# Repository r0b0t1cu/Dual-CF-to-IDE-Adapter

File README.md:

# Dual CF-to-IDE Adapter

A dual CompactFlash-to-IDE adapter designed to connect two CF cards to a standard 40-pin IDE interface. Each CF slot can be configured independently as **Master**, **Slave**, or **Cable Select**. The board also provides selectable CF supply voltage and selectable power input.

The project is intended for vintage-computing and other systems that use an IDE interface.

## Features

- Two CompactFlash card slots (Slot A and Slot B).
- Independent Master / Slave / Cable Select configuration for each slot.
- Selectable CF supply voltage: **5 V or 3.3 V**.
- Selectable power source: external +5 V input or power from IDE pin 20.
- Four status LEDs:
  - **POWER** – board power indication.
  - **MASTER** – lit when a card is present in slot A.
  - **SLAVE** – lit when a card is present in slot B.
  - **ACTIVITY** – drive activity indication (shared DASP# line; lit during access by either card, if the card drives DASP#).
- Polyfuse protection on the power input.
- KiCad design files, schematic, BOM, assembly documentation and PCB manufacturing files included.

## Configuration

**Set the jumpers before powering the adapter.**

### JP1 – Power Select

Selects the source for the board's +5 V supply:

| JP1 position | Power source |
|---|---|
| Pins 1–2 | External +5 V input via J5 |
| Pins 2–3 | IDE connector pin 20 |

J5 is the two-pin external power connector and is marked `+5V` on the PCB. Use only the selected power source; do not connect external power and IDE pin-20 power at the same time.

### JP2 – CF supply voltage

Selects the supply voltage provided to the CF interface:

| JP2 position | CF supply |
|---|---|
| Pins 1–2 | 5 V |
| Pins 2–3 | 3.3 V |

**Check the voltage requirement of your CF card before setting JP2.** Do not assume that every CompactFlash card accepts both supply voltages.

### JP3 – Slot A (Master/Slave)

| JP3 position | Slot A configuration |
|---|---|
| Pins 1–2 | Master |
| Pins 2–3 | Cable Select |
| Open (no jumper) | Slave |

### JP4 – Slot B (Master/Slave)

| JP4 position | Slot B configuration |
|---|---|
| Pins 1–2 | Master |
| Pins 2–3 | Cable Select |
| Open (no jumper) | Slave |

The two slots have independent device-select jumpers. When using both cards on the same IDE channel, configure them so that they do not both claim the same device role (for example, one Master and the other Slave), subject to the host system's IDE support.
The CF A / CF B LEDs follow the physical slot, not the Master/Slave role set by JP3/JP4.

## Connectors and indicators

| Reference | Description |
|---|---|
| J2 | 40-pin IDE interface |
| J3 | CompactFlash Slot A |
| J4 | CompactFlash Slot B |
| J5 | External +5 V power input |
| JP1 | Power-source selection |
| JP2 | CF supply-voltage selection |
| JP3 | Slot A device selection |
| JP4 | Slot B device selection |
| D2 | POWER LED |
| D3 | CF A card-present LED |
| D4 | CF B card-present LED |
| D5 | ACTIVITY LED |

---

If you enjoy my projects and would like to support my work, you can do so through PCBWay. You can also order the PCBs for this project directly from the link below. Every bit of support is appreciated!

<p>
  
</p>

---

## Bill of Materials

The component list is available in two formats:

- [`bom/ibom.html`](bom/ibom.html) – interactive Bill of Materials.
- [`production/bom.csv`](production/bom.csv) – CSV component list.

The BOM includes the two CF connectors, IDE socket, power and configuration headers, AMS1117-3.3 regulator, capacitors, resistors, LEDs and a polyfuse. Check the BOM and the PCB silkscreen when sourcing and assembling components.

## PCB fabrication

The `production/` directory contains the fabrication archive and supporting production data:

- `Dual-CF-to-IDE_Adapter_v1.zip` – PCB manufacturing files.
- `bom.csv` – component list.
- `designators.csv` – component designators.
- `netlist.ipc` – IPC netlist.
- `positions.csv` – component placement data.

Confirm the fabrication archive and the requirements of your PCB manufacturer before placing an order.

## Assembly and first power-up

1. Assemble the PCB using the schematic and BOM.
2. Check the orientation of the CF connectors, LEDs, electrolytic capacitors and voltage regulator.
3. Inspect the board for solder bridges, shorts and incorrect component placement.
4. Set JP1 to the intended power source.
5. Set JP2 to the voltage required by the CF card(s).
6. Set JP3 and JP4 for the intended Master/Slave/Cable Select arrangement.
7. Verify the selected supply voltage and polarity before inserting cards and connecting the adapter to the host.

If you are unsure about the host's IDE pin-20 wiring or the CF card's voltage requirements, verify these details before applying power.

## Documentation and photos

- [Schematic PDF](doc/Dual-CF-to-IDE_Adapter_v1.pdf)
- [Interactive BOM](bom/ibom.html)

Board photographs:

## Design files

The hardware design is provided as KiCad project, schematic and PCB files in `Dual-CF-to-IDE_Adapter_v1/`. (needs KiCad 10)

## License

The hardware design files in this project are released under the **CERN Open Hardware Licence Version 2 – Strongly Reciprocal (CERN-OHL-S-2.0)**. See the [`LICENSE`](LICENSE) file for the complete licence text.

This licence allows the design to be used, studied, modified, manufactured and redistributed, including commercially. If you distribute modified design files or products based on this design, the licence requires you to make the corresponding complete source available under the same licence and preserve the applicable notices.

Third-party components, libraries and other materials included in the repository may be subject to their own licences; those remain applicable to their respective materials.

Copyright (C) 2026 r0b0t1cu

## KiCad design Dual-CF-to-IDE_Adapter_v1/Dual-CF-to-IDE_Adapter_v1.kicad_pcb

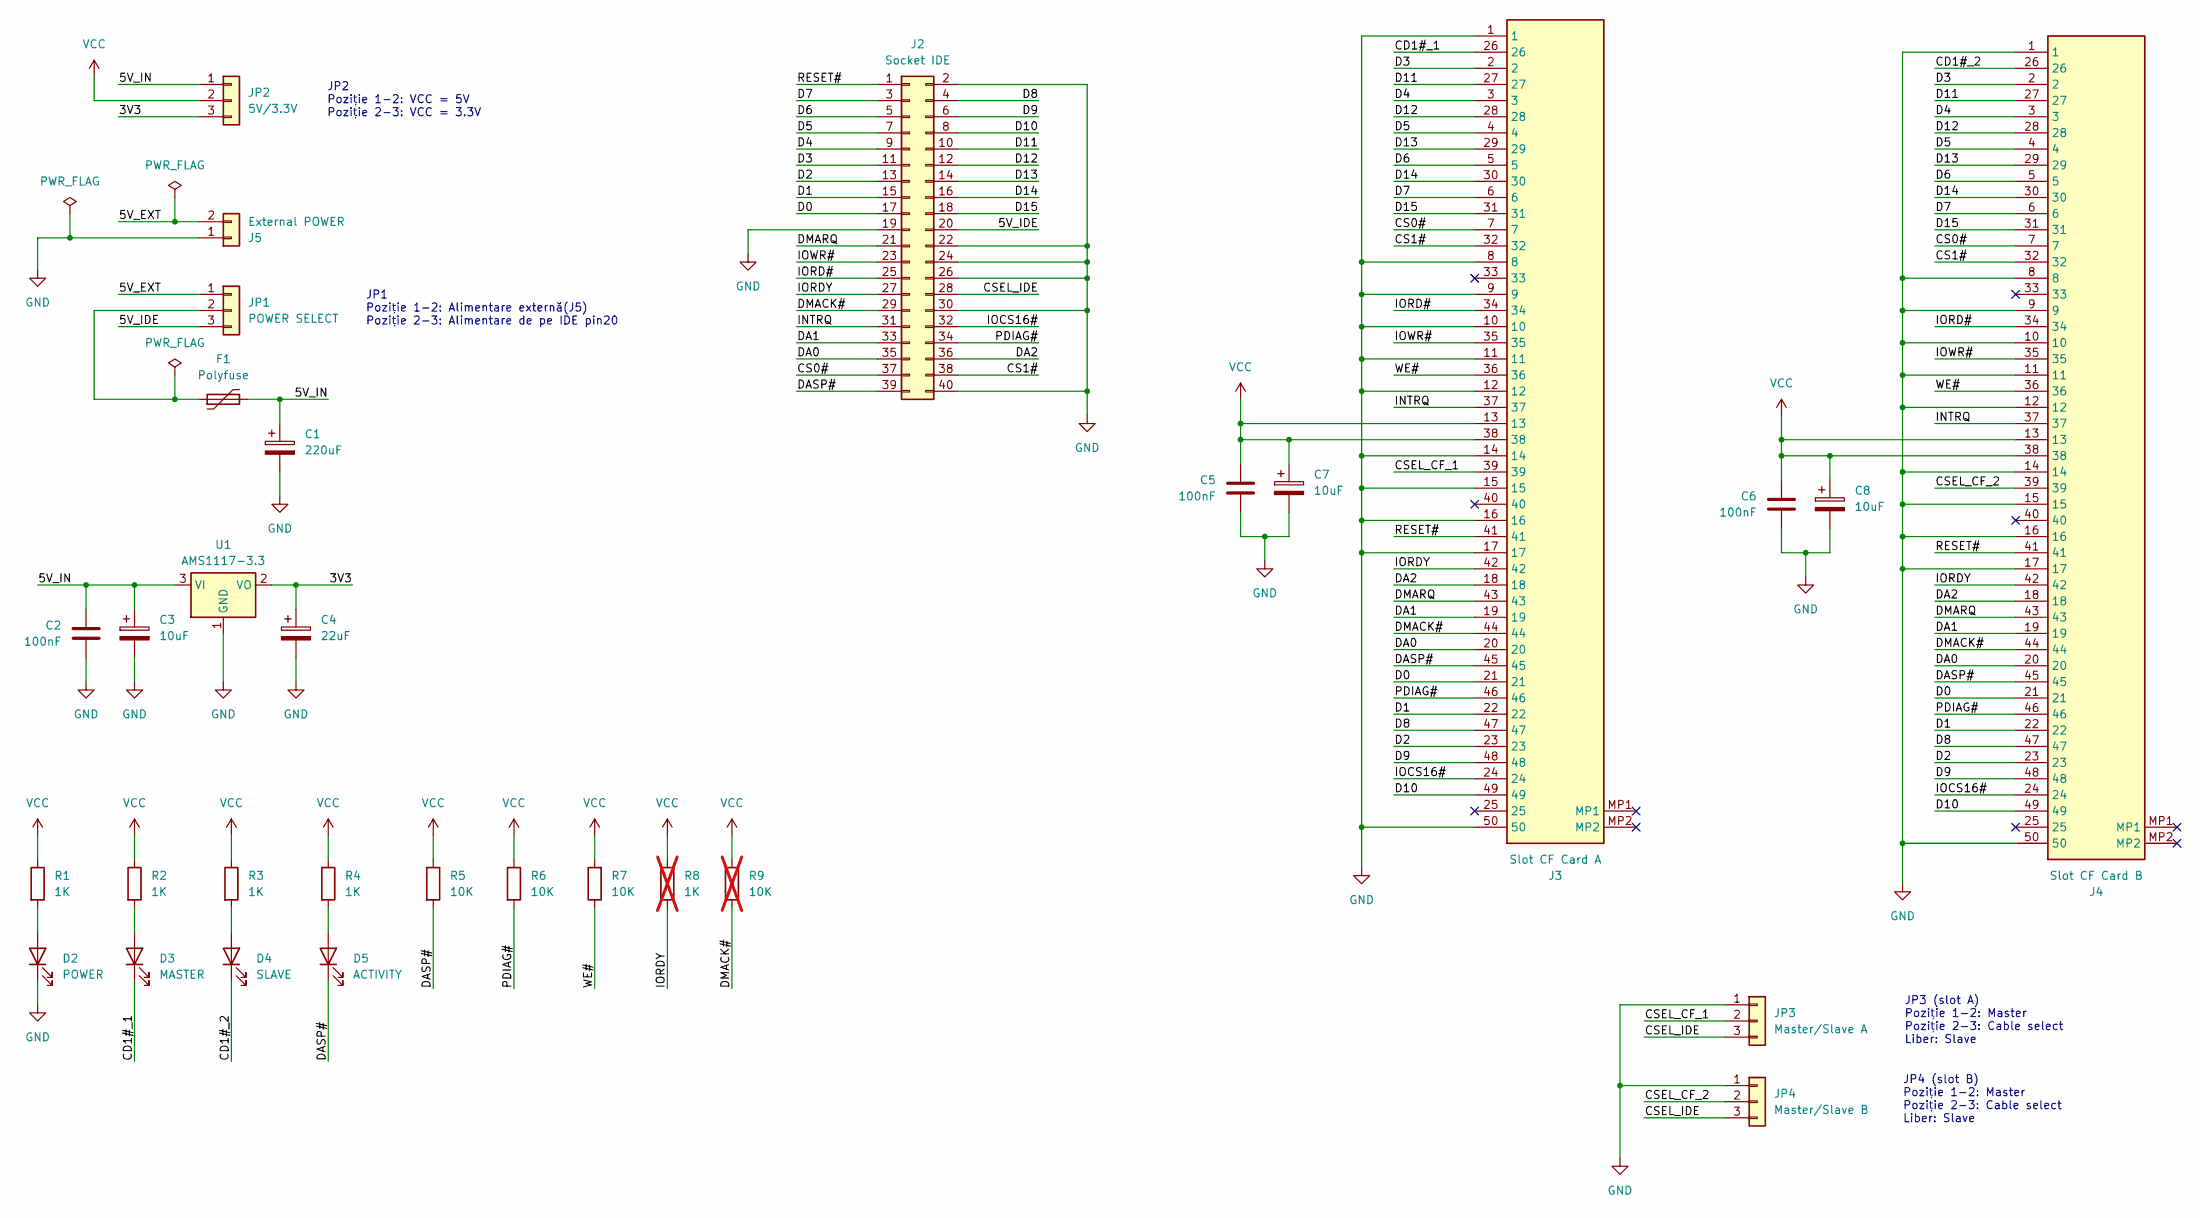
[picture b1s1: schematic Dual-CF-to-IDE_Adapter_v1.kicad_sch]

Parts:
C1: 220uF; CP_Radial_D5.0mm_P2.00mm
C2, C5, C6: 100nF; C_1206_3216Metric
C3, C7, C8: 10uF; CP_Radial_D5.0mm_P2.00mm
C4: 22uF; CP_Radial_D5.0mm_P2.00mm
D2: POWER; LED_D3.0mm
D3: MASTER; LED_D3.0mm
D4: SLAVE; LED_D3.0mm
D5: ACTIVITY; LED_D3.0mm
F1: Polyfuse; R_Axial_DIN0204_L3.6mm_D1.6mm_P7.62mm_Horizontal
J2: Socket IDE; PinSocket_2x20_P2.54mm_Horizontal
J3: Slot CF Card A; 101DTAABR01-40.16; Manufacturer_Part_Number 101D-TAAB-R01
J4: Slot CF Card B; 101DTAABR01-40.16; Manufacturer_Part_Number 101D-TAAB-R01
J5: External POWER; PinHeader_1x02_P2.54mm_Horizontal
JP1: POWER SELECT; PinHeader_1x03_P2.54mm_Vertical
JP2: 5V/3.3V; PinHeader_1x03_P2.54mm_Vertical
JP3: Master/Slave A; PinHeader_1x03_P2.54mm_Vertical
JP4: Master/Slave B; PinHeader_1x03_P2.54mm_Vertical
R1, R2, R3, R4: 1K; R_0805_2012Metric
R5, R6, R7: 10K; R_0805_2012Metric
R8: 1K; R_0805_2012Metric; not fitted
R9: 10K; R_0805_2012Metric; not fitted
U1: AMS1117-3.3; SOT-223-3_TabPin2

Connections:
/3V3: C4.1, JP2.3, U1.2 (VO)
/5V_EXT: J5.2, JP1.1
/5V_IDE: J2.20, JP1.3
/5V_IN: C1.1, C2.1, C3.1, F1.2, JP2.1, U1.3 (VI)
/CD1#_1: D3.1 (K), J3.26
/CD1#_2: D4.1 (K), J4.26
/CS0#: J2.37, J3.7, J4.7
/CS1#: J2.38, J3.32, J4.32
/CSEL_CF_1: J3.39, JP3.2
/CSEL_CF_2: J4.39, JP4.2
/CSEL_IDE: J2.28, JP3.3, JP4.3
/D0: J2.17, J3.21, J4.21
/D1: J2.15, J3.22, J4.22
/D2: J2.13, J3.23, J4.23
/D3: J2.11, J3.2, J4.2
/D4: J2.9, J3.3, J4.3
/D5: J2.7, J3.4, J4.4
/D6: J2.5, J3.5, J4.5
/D7: J2.3, J3.6, J4.6
/D8: J2.4, J3.47, J4.47
/D9: J2.6, J3.48, J4.48
/D10: J2.8, J3.49, J4.49
/D11: J2.10, J3.27, J4.27
/D12: J2.12, J3.28, J4.28
/D13: J2.14, J3.29, J4.29
/D14: J2.16, J3.30, J4.30
/D15: J2.18, J3.31, J4.31
/DA0: J2.35, J3.20, J4.20
/DA1: J2.33, J3.19, J4.19
/DA2: J2.36, J3.18, J4.18
/DASP#: D5.1 (K), J2.39, J3.45, J4.45, R5.2
/DMACK#: J2.29, J3.44, J4.44, R9.2
/DMARQ: J2.21, J3.43, J4.43
/INTRQ: J2.31, J3.37, J4.37
/IOCS16#: J2.32, J3.24, J4.24
/IORD#: J2.25, J3.34, J4.34
/IORDY: J2.27, J3.42, J4.42, R8.2
/IOWR#: J2.23, J3.35, J4.35
/PDIAG#: J2.34, J3.46, J4.46, R6.2
/RESET#: J2.1, J3.41, J4.41
/WE#: J3.36, J4.36, R7.1
GND: C1.2, C2.2, C3.2, C4.2, C5.2, C6.2, C7.2, C8.2, D2.1 (K), J2.2, J2.19, J2.22, J2.24, J2.26, J2.30, J2.40, J3.1, J3.8, J3.9, J3.10, J3.11, J3.12, J3.14, J3.15, J3.16, J3.17, J3.50, J4.1, J4.8, J4.9, J4.10, J4.11, J4.12, J4.14, J4.15, J4.16, J4.17, J4.50, J5.1, JP3.1, JP4.1, U1.1 (GND)
unnamed: D2.2 (A), R1.2
unnamed: D3.2 (A), R2.2
unnamed: D4.2 (A), R3.2
unnamed: D5.2 (A), R4.2
unnamed: F1.1, JP1.2
VCC: C5.1, C6.1, C7.1, C8.1, J3.13, J3.38, J4.13, J4.38, JP2.2, R1.1, R2.1, R3.1, R4.1, R5.1, R6.1, R7.2, R8.1, R9.1

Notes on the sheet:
JP4 (slot B) Poziție 1-2: Master Poziție 2-3: Cable select Liber: Slave
JP1 Poziție 1-2: Alimentare externă(J5) Poziție 2-3: Alimentare de pe IDE pin20
JP3 (slot A) Poziție 1-2: Master Poziție 2-3: Cable select Liber: Slave
JP2 Poziție 1-2: VCC = 5V Poziție 2-3: VCC = 3.3V

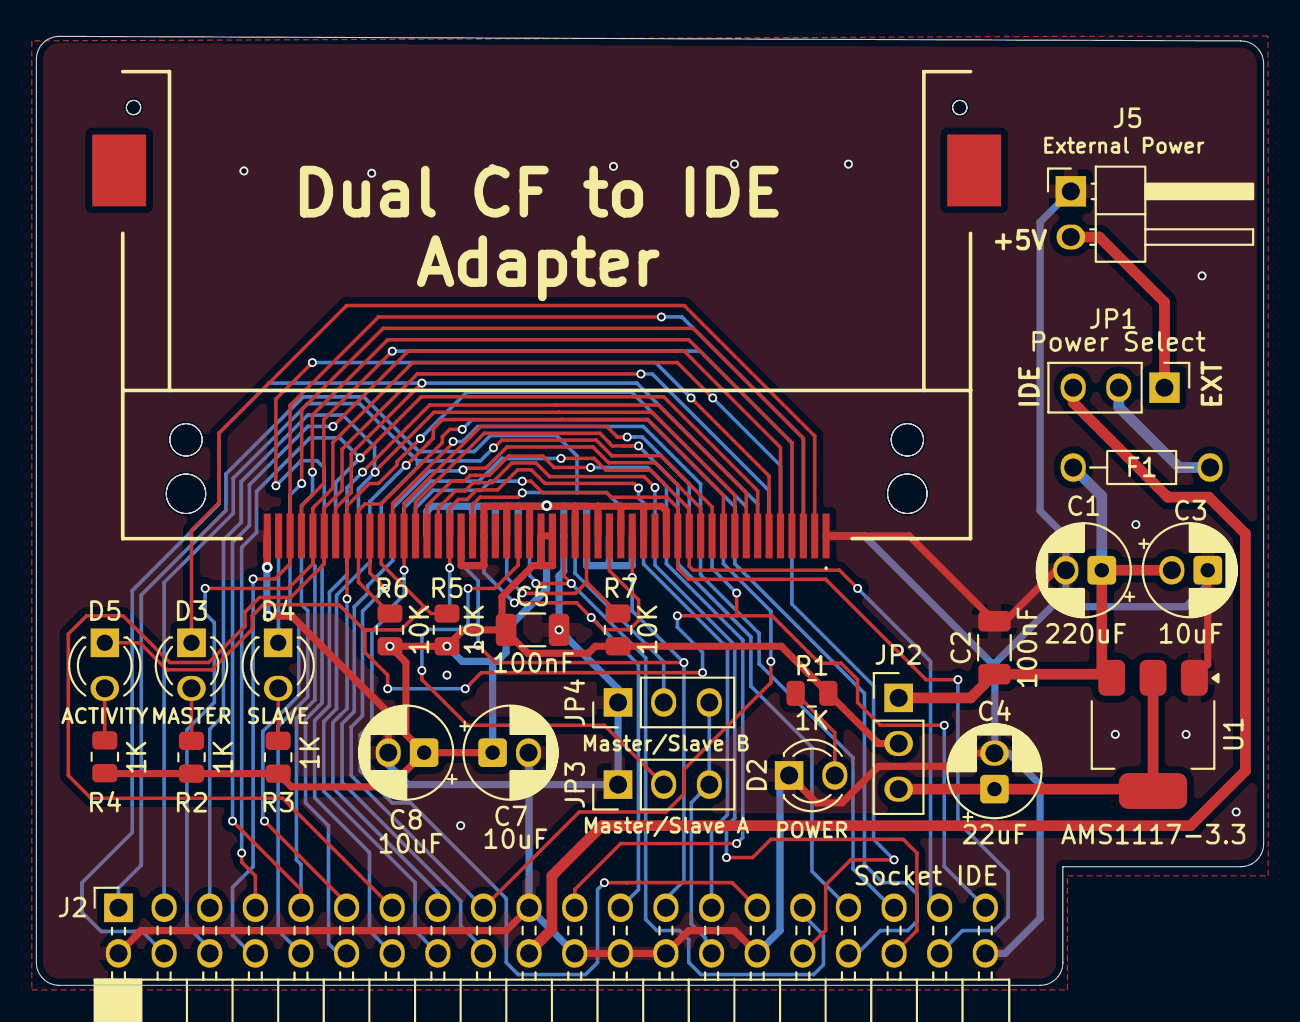
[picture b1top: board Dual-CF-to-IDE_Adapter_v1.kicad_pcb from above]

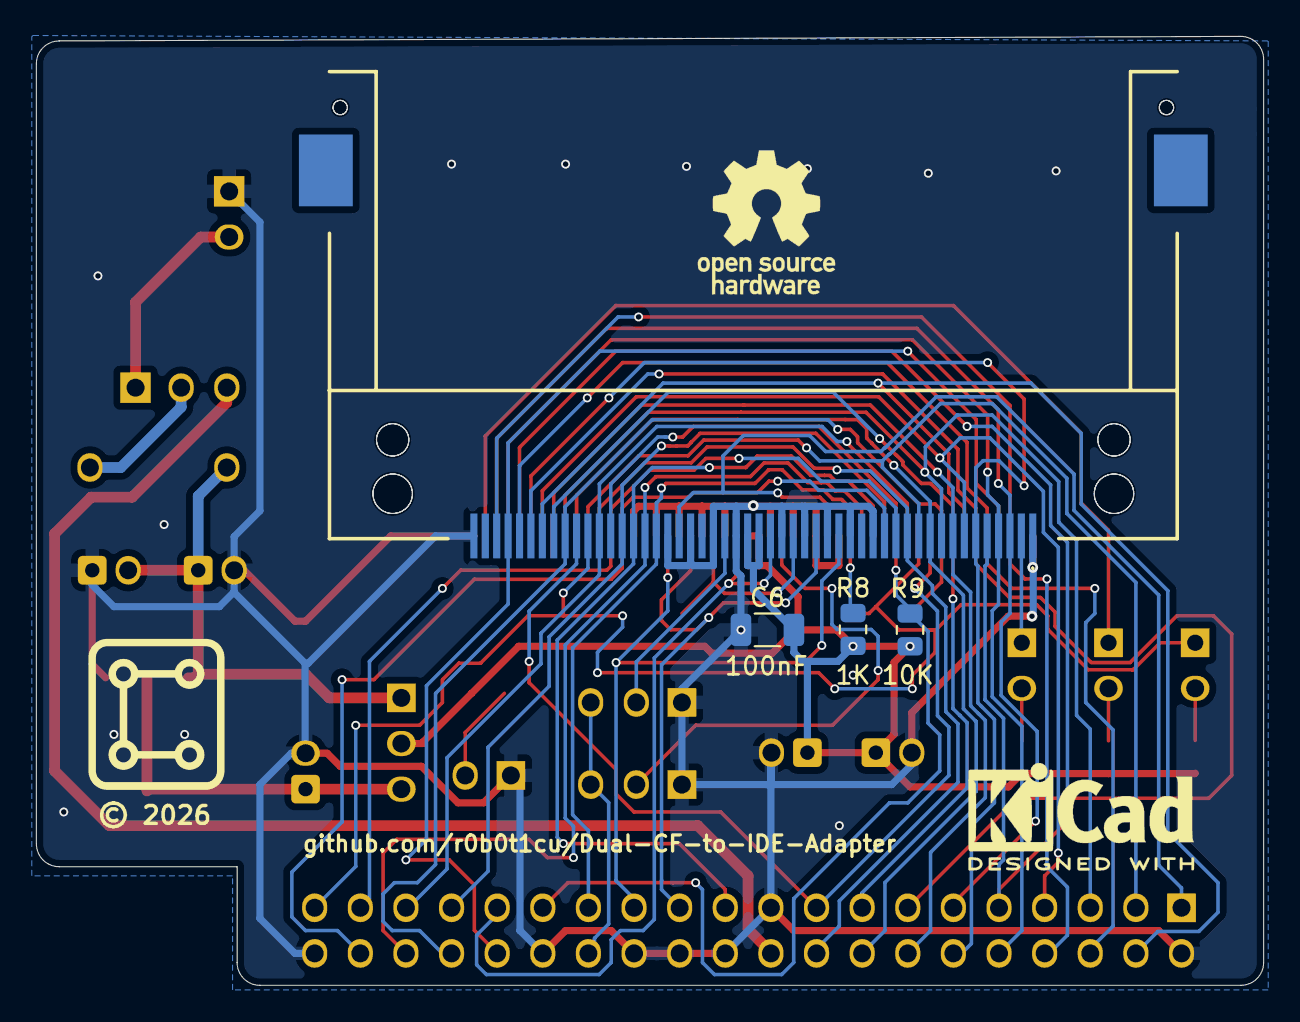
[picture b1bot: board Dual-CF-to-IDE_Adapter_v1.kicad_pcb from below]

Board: 2 copper layers, 68.3 x 52.8 mm, 31 parts (4 on the bottom side), 48 nets.

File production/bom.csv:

Designator,Footprint,Quantity,Value,LCSC Part #
C1,CP_Radial_D5.0mm_P2.00mm,1,220uF,
"C2, C5, C6",1206,3,100nF,
"C3, C7, C8",CP_Radial_D5.0mm_P2.00mm,3,10uF,
C4,CP_Radial_D5.0mm_P2.00mm,1,22uF,
D2,LED_D3.0mm,1,POWER,
D3,LED_D3.0mm,1,MASTER,
D4,LED_D3.0mm,1,SLAVE,
D5,LED_D3.0mm,1,ACTIVITY,
F1,R_Axial_DIN0204_L3.6mm_D1.6mm_P7.62mm_Horizontal,1,Polyfuse,
J2,PinSocket_2x20_P2.54mm_Horizontal,1,Socket IDE,
J3,101DTAABR01-40.16,1,Slot CF Card A,
J4,101DTAABR01-40.16,1,Slot CF Card B,
J5,PinHeader_1x02_P2.54mm_Horizontal,1,External Power,
JP1,PinHeader_1x03_P2.54mm_Vertical,1,Power Select,
JP2,PinHeader_1x03_P2.54mm_Vertical,1,5V/3.3V,
JP3,PinHeader_1x03_P2.54mm_Vertical,1,Master/Slave A,
JP4,PinHeader_1x03_P2.54mm_Vertical,1,Master/Slave B,
"R1, R2, R3, R4, R8",0805,5,1K,
"R5, R6, R7, R9",0805,4,10K,
U1,SOT-223-3_TabPin2,1,AMS1117-3.3,

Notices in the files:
Dual-CF-to-IDE_Adapter_v1/Dual-CF-to-IDE_Adapter_v1.kicad_pcb:
© 2026
